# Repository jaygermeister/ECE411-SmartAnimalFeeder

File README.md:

# ECE411 Smart Animal Feeder

The Smart Animal Feeder is a comprehensive solution that caters to the diverse needs of pets in a household. It brings convenience, efficiency, and peace of mind to pet owners, ensuring that feeding time becomes a harmonious and stress-free experience.

The product will be designed as a team effort for ECE411 of Fall 2023 at Portland State University.

Team 13 is under the instruction of Andrew Greenberg.

## Team Members:
- Isaac Miller
- Brian Bach
- James Best
- Tommy Lee

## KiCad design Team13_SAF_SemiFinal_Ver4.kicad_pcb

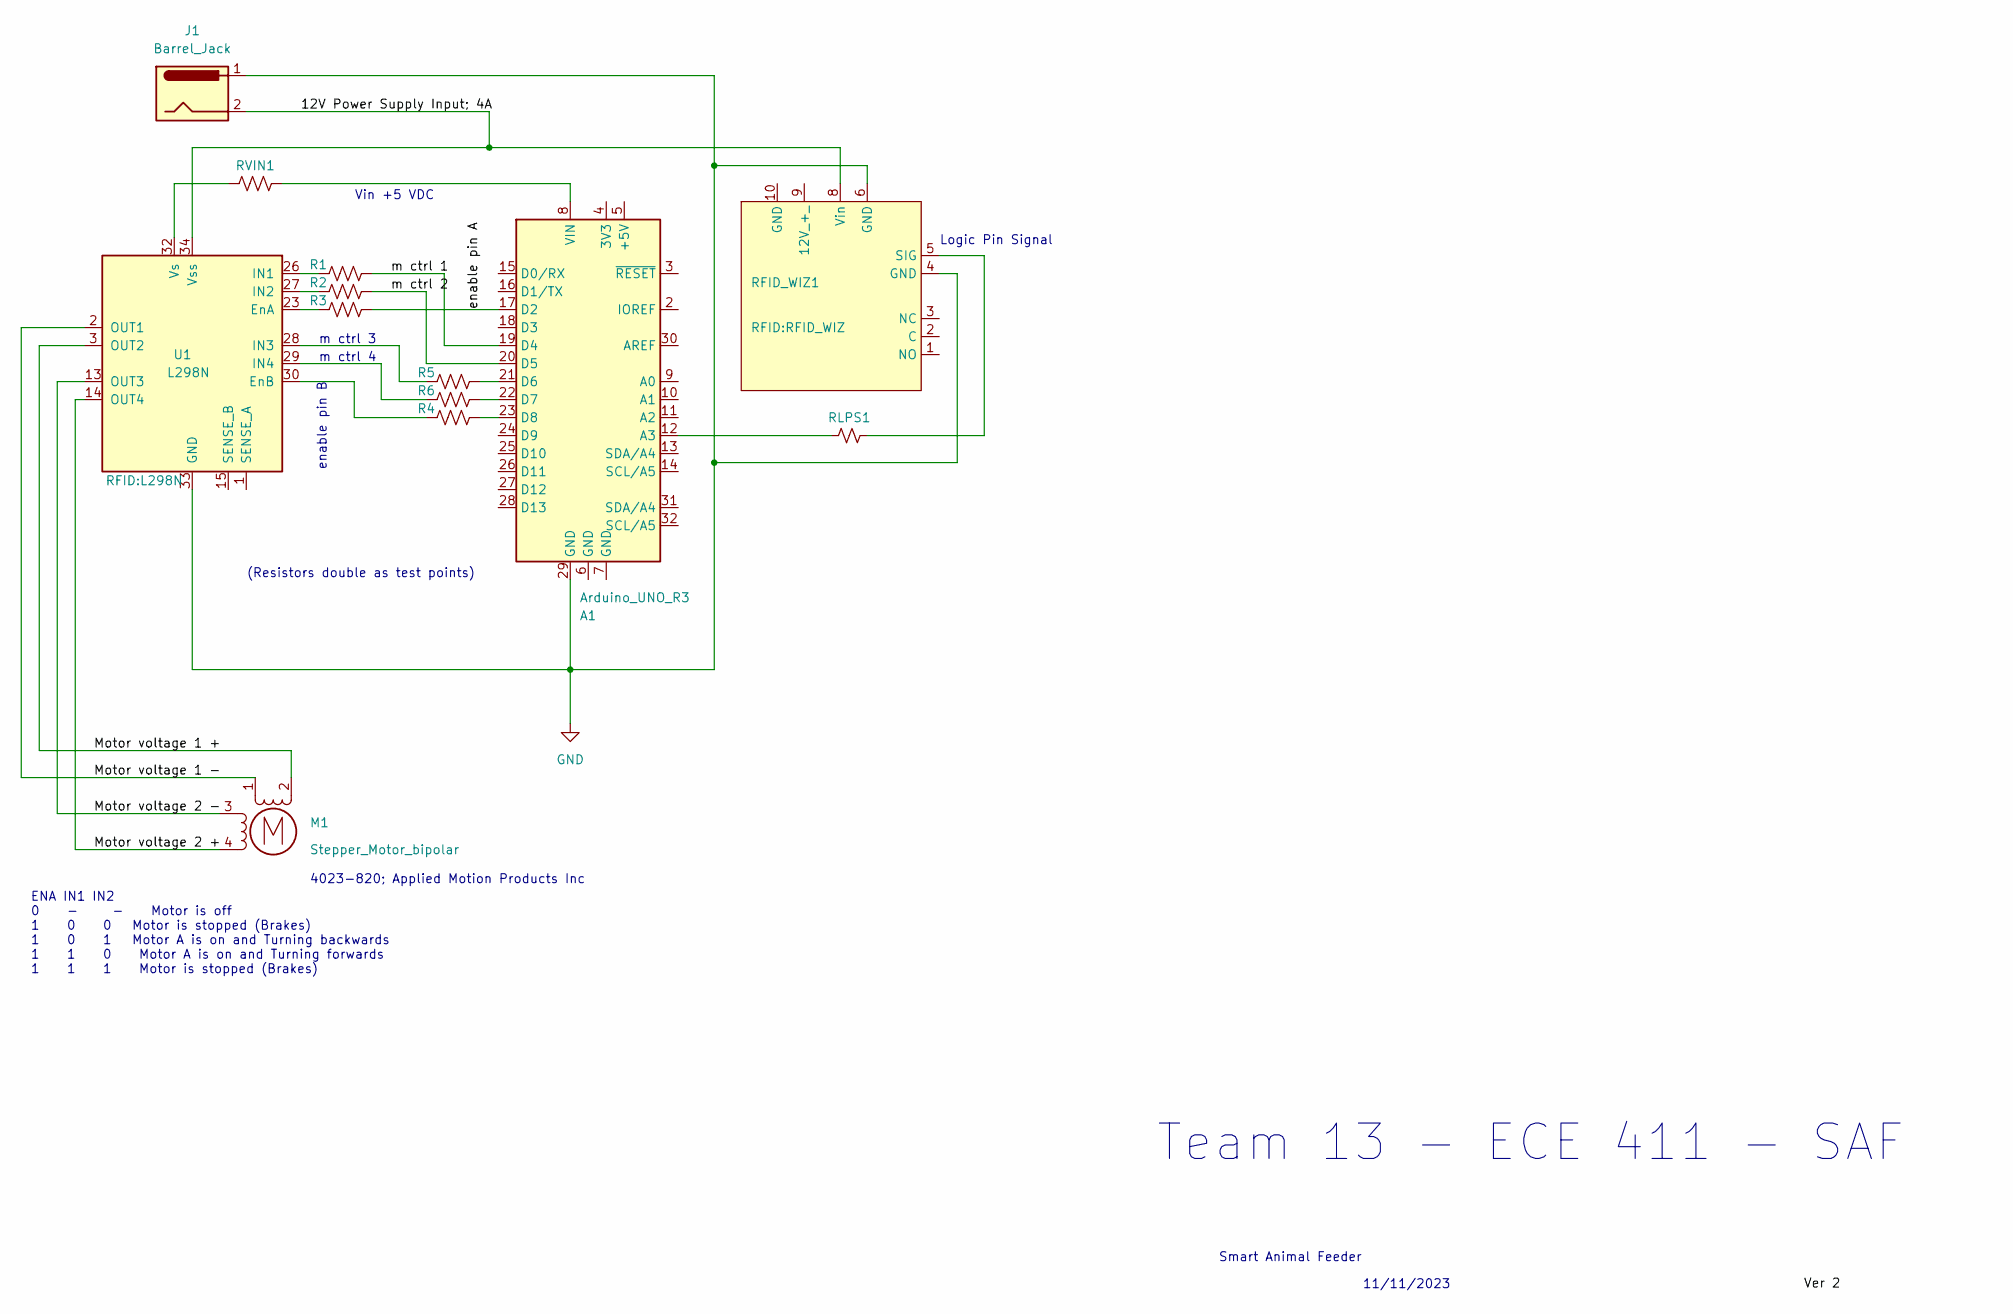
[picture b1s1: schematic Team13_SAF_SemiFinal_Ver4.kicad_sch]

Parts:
A1: Arduino_UNO_R3; Arduino_UNO_R3_WithMountingHoles
J1: Barrel_Jack; BarrelJack_GCT_DCJ200-10-A_Horizontal
M1: Stepper_Motor_bipolar
R1, R2, R3, R4, R5, R6: R_US; R_0402_1005Metric
RFID_WIZ1: RFID_WIZ
RLPS1: R_Small_US; R_0402_1005Metric
RVIN1: R_US; R_0603_1608Metric
U1: L298N

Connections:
/12V Power Supply Input; 4A: J1.2, RFID_WIZ1.8 (Vin), U1.34 (Vss)
/Motor voltage 1 +: M1.2 (-), U1.3 (OUT2)
/Motor voltage 1 -: M1.1, U1.2 (OUT1)
/Motor voltage 2 +: M1.4, U1.14 (OUT4)
/Motor voltage 2 -: M1.3, U1.13 (OUT3)
/enable pin A: A1.17 (D2), R3.1
/m ctrl 1: A1.19 (D4), R1.1
/m ctrl 2: A1.20 (D5), R2.1
GND: A1.29 (GND), J1.1, RFID_WIZ1.4 (GND), RFID_WIZ1.6 (GND), RFID_WIZ1.9 (12V_+_), U1.33 (GND)
unnamed: A1.12 (A3), RLPS1.2
unnamed: A1.21 (D6), R5.1
unnamed: A1.22 (D7), R6.1
unnamed: A1.23 (D8), R4.1
unnamed: A1.8 (VIN), RVIN1.1
unnamed: RFID_WIZ1.5 (SIG), RLPS1.1
unnamed: R3.2, U1.23 (EnA)
unnamed: R4.2, U1.30 (EnB)
unnamed: R1.2, U1.26 (IN1)
unnamed: R2.2, U1.27 (IN2)
unnamed: R5.2, U1.28 (IN3)
unnamed: R6.2, U1.29 (IN4)
unnamed: RVIN1.2, U1.32 (Vs)

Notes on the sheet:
(Resistors double as test points)
m ctrl 3
Logic Pin Signal
Smart Animal Feeder
4023-820; Applied Motion Products Inc
Vin +5 VDC
enable pin B
ENA IN1 IN2 0 - - Motor is off 1 0 0 Motor is stopped (Brakes) 1 0 1 Motor A is on and Turning backwards 1 1 0 Motor A is on and Turning forwards 1 1 1 Motor is stopped (Brakes)
11/11/2023
Team 13 - ECE 411 - SAF
m ctrl 4

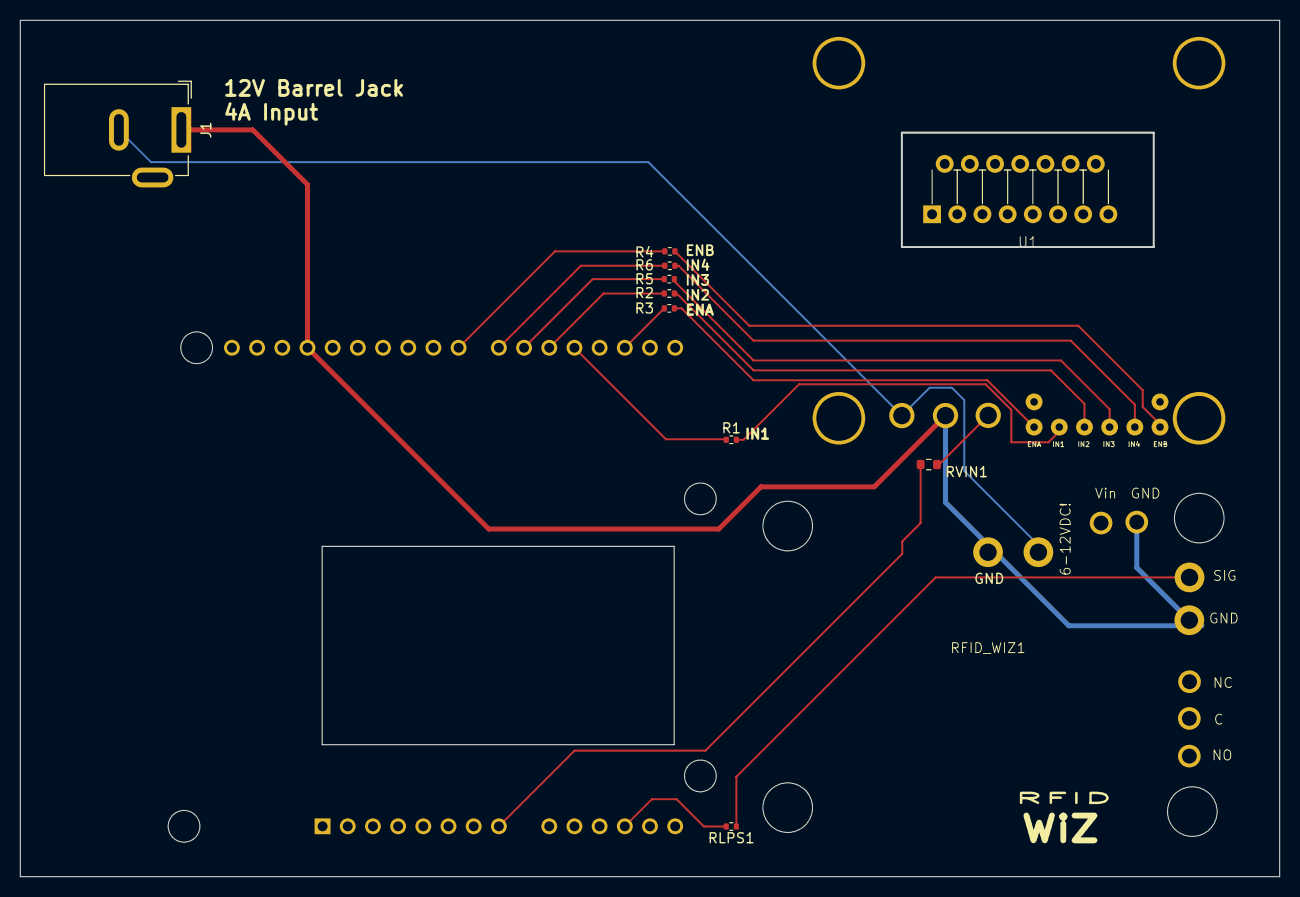
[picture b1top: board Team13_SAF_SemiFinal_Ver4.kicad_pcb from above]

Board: 2 copper layers, 127.0 x 86.4 mm, 12 parts (1 on the bottom side), 18 nets.

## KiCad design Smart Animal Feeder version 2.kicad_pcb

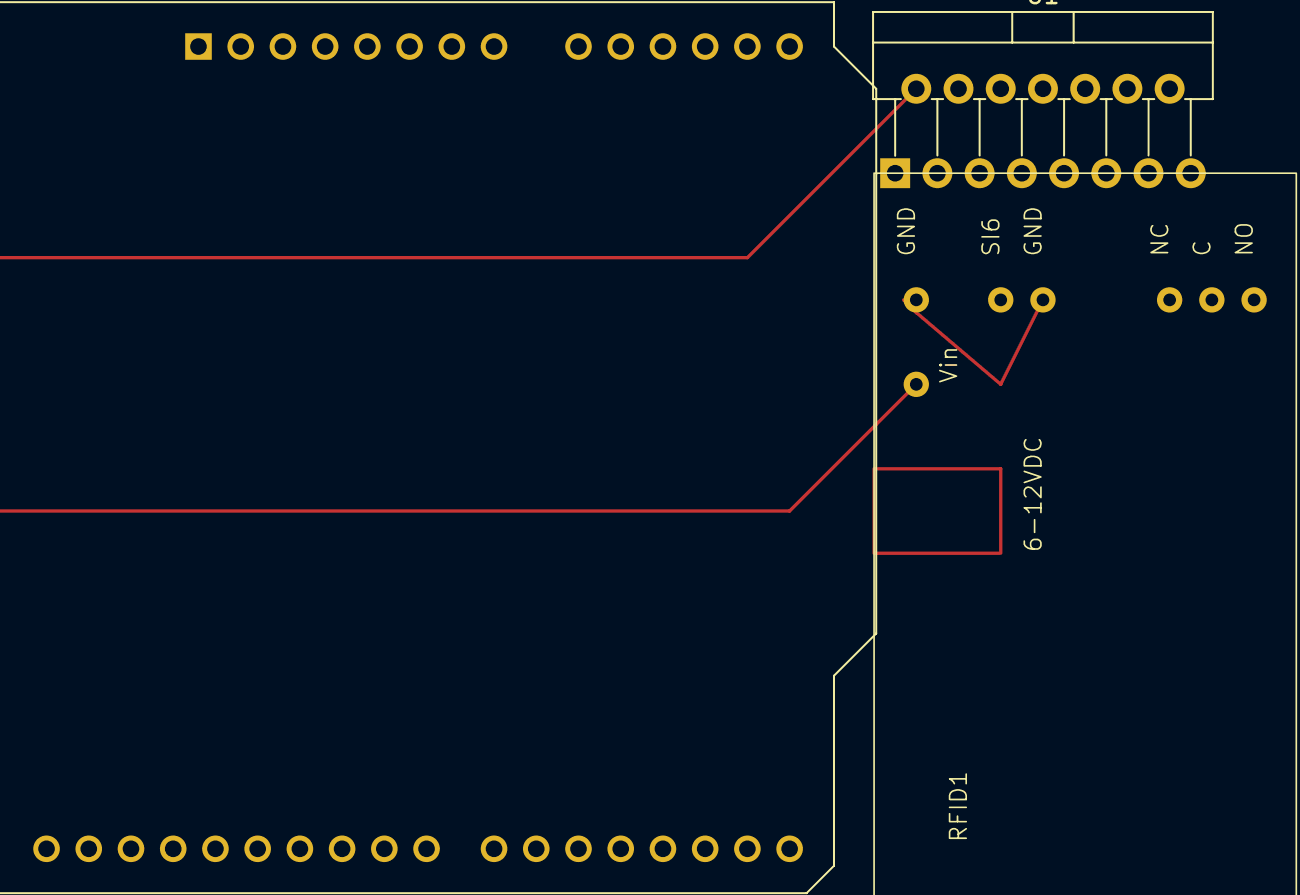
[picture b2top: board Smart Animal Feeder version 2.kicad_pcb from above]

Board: 2 copper layers, 3 parts (0 on the bottom side), 4 nets.

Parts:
A1: Arduino_UNO_R3
RFID1: RFID_Wizkit
U1: L298N; TO-220-15_P2.54x2.54mm_StaggerOdd_Lead4.58mm_Vertical

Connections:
/Enable pin A: A1.17 (D2), U1.6 (EnA)
/Motor Control 1: A1.15 (D0/RX), U1.5 (IN1)
/Motor Control 2: A1.16 (D1/TX), U1.7 (IN2)
GND: A1.8 (VIN), A1.29 (GND), U1.8 (GND), U1.9 (Vss)

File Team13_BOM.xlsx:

Bill Of Materials for: [Team 13] [Smart Animal Feeder]
Last modified: [08 November 2023]
PCB version: [PCB VERSION #1]
BOM revision: [BOM REVISION #1] |  | P/NP | = Place/Not Place (components marked NP are not stuffed on the board)
Cnt | Part References | P/NP | Mfg | Mfg PN | Description | Dist | Dist Part Number | Cost Ea. | Cost Total
1.0 | NA | NP | Zevro | KCH-06114 | Food Dispenser Single Control | Amazon | B00013K8O4 | 17.72 | 17.72
1.0 | RFID1 | P/NP | Smooth Technology | 5402.0 | RFID Kit with multiple contents inside | Adafruit | 5402.0 | 49.95 | 49.95
1.0 | M1 | NP | Toshiba | TA8080K | TA8080K Motor Driver With Brake Function | Applied Motion Products Inc. | 4023-820 | 9.99 | 9.99
1.0 | A1 | NP | Elegoo | EL-CB-001 | Arduino UNO R3 Board | Elegoo | EL-CB-001 | 18.0 | 18
1.0 | U1 | NP | Qunqi | MK-050 | H Bridge Driver for DC Stepper For Arduino | Amazon | ‎CECOMINOD012186 | 6.99 | 6.99
 |  |  |  |  |  |  |  | TOTAL: | 102.65
VERSION INFO
Rev | Date | Notes
1.0r1 | 45238.0 | Cleaned up parts, rough draft of board
1.0r0 | 45235.0 | Initial BOM

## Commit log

2023-10-12 Update README.md
    Create a collaboration site for your team. The collaboration site must:
    Have version (“revision”) control
    Support collaborative documentation (e.g., markdown files, wiki, HTML pages)
    Have some kind of issue tracking
    For example, a freely available Github site matches all of these requirements, which is what we'll officially support in ECE411. Your repository can be public (don’t forget to choose a license!) or i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
2023-10-18 Creating Product Design Specifications
    Added the Product Design Spec sections:
    Executive Summary and Theory of Operation
    Brief Market Analysis
    section headers as outline
2023-10-18 Update Product Design Specifications
    Added some formatting and organized sections for better visual queue
2023-10-18 Rename Product Design Specifications to Product Design Specifications.md
2023-10-19 Update Product Design Specifications.md
    Added Design Specification Bullet list
2023-10-19 Update Product Design Specifications.md
    removed excessive header. Cleaned up formatting
2023-10-19 Update Design Specifications sections.md
    grammer changes/phrasing updates
    streamlined for conciseness
2023-10-19 Update Product Design Specifications.md
    adding the block diagram
2023-10-26 Add files via upload
    Preliminary detailed schematic
2023-11-02 Updated Schematic 1 - SAF - Team 13-pdf.jpg
    The new and improved schematic
2023-11-02 Add files via upload
    Updated Schematic
2023-11-09 Add files via upload
    Schematic version 2. The motor has been selected and the driver selection updated.
    Signal labels were added and logic table will be added next revision.
2023-11-09 Functional Decomposition
    Detailed Lv0 and Lv1 diagram for the RFID reader and Motor Controller.
2023-11-09 Add files via upload
    Level 0 and Level 1 block diagram showing inputs and outputs.
    Interconnections labeled and formatting applied according to lecture slides for WK7 -ECE 411
2023-11-09 Add files via upload
    PCB 1st draft. Routing needs attention and finalized
    Need to create power delivery with appropriate traces for current and voltage ratings and routing to subsystems
2023-11-09 Add files via upload
    PCB version of 1st draft CAD brd file
2023-11-11 Add files via upload
    Revised Schematic for parts. Added power lines and descriptions. Included truth table for motor control from Microcontroller.
2023-11-13 Add files via upload
    Semi Final PCB design for team review.
    Added mounting holes for individual modules
    trace routing for all signals
    PCB cutouts for module pin clearance for existing solder work
    Routing for 12V power Delivery
    Routing for 5-7V from L298N to Supply power to Arduino
2023-11-13 Semi Final draft of Schematic for Review
2023-11-14 PDF of layout file
    Printer ready version of the PCB layout for SAF. Needs final review this week (11/14)
2023-11-14 Schematic PDF for review
2023-11-16 uploading Wk 08 files
    Adding pdf schematic final version
    adding pdf of layout final version
    attaching kicad sketch files to preserve on cloud
2023-12-04 Create Arduino_Code
    This is the bare minimum code for the arduino to collect the signal state from the RFID WIZ and determine if the motor should be turned.
2023-12-04 Delete Schematic - SAF - SemiFinal - Ver4.pdf
    cleaning up earlier revs
2023-12-04 Delete Schematic 1 - SAF - Team 13 Version 2.pdf
    cleaning up obsolete revision numbers
2023-12-04 Delete Schematic 1 - SAF - Team 13 Version 3.pdf
    cleaning up obsolete files
2023-12-04 Delete Schematic 1 - SAF - Team 13.pdf
    deleting obsolete revisions
2023-12-04 Delete Smart Animal Feeder version 2.kicad_pcb
    cleaning up obsolete files
2023-12-04 Delete Team 13 - CAD 1 - PCB.pdf
    deleting obsolete files
2023-12-04 Delete Team13_SAF_SemiFinal_Ver4.kicad_pcb
    deleting obsolete files
2023-12-04 Cleaning up Obsolete Files
    Version updated to Alpha Test phase
2023-12-08 Update Arduino_Code
    Added early form of time scheduling, commented out. No actual changes to runnable code.
